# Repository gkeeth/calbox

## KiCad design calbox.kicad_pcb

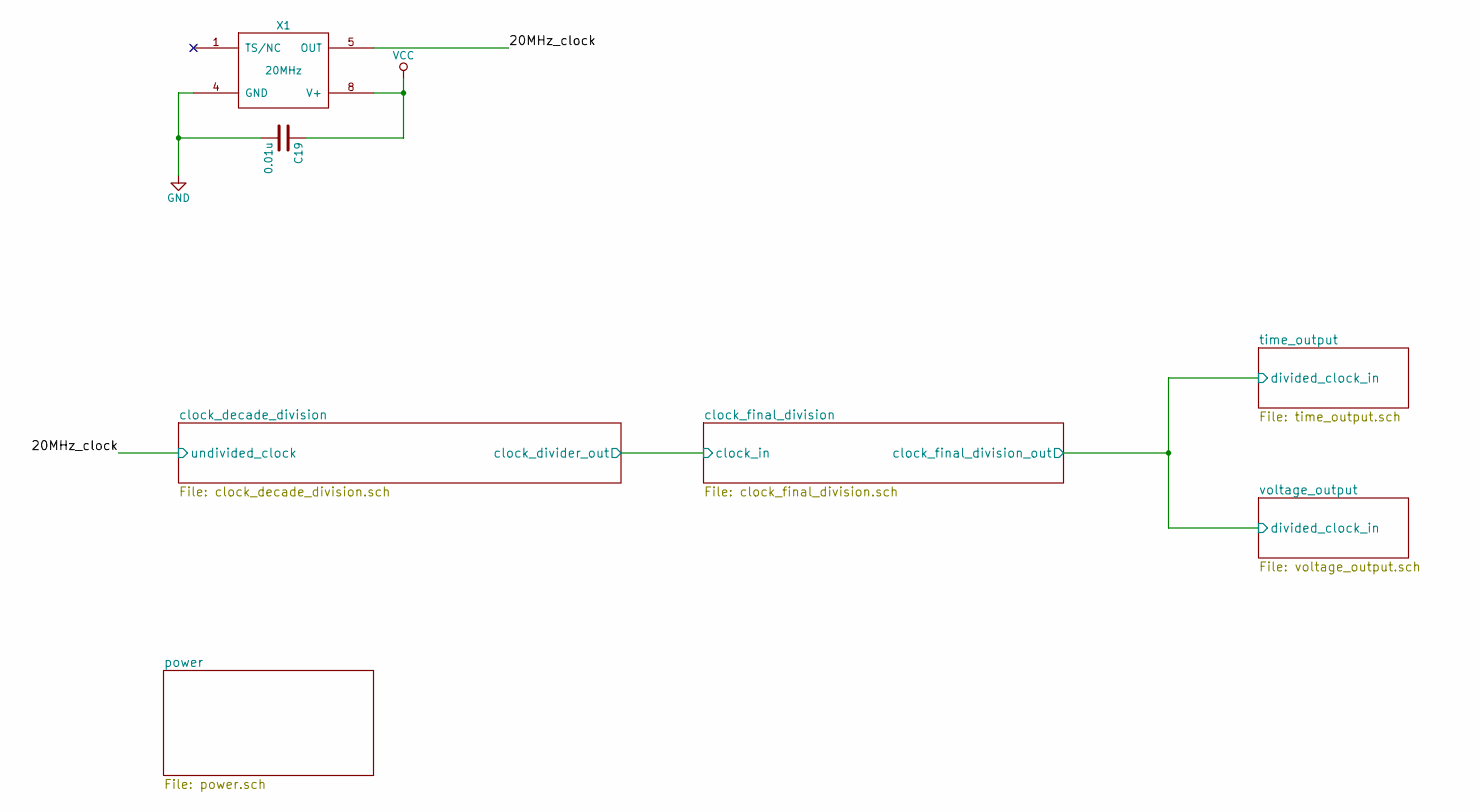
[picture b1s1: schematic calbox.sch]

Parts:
C19: 0.01u; C_0805_HandSoldering
X1: 20MHz; OSC_DIP8; Manufacturer PN ACHL-20.000MHZ-EK

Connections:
/20MHz_clock: X1.5 (OUT); also elsewhere on the board
GND: C19.2, X1.4 (GND); also elsewhere on the board
VCC: C19.1, X1.8 (V+); also elsewhere on the board

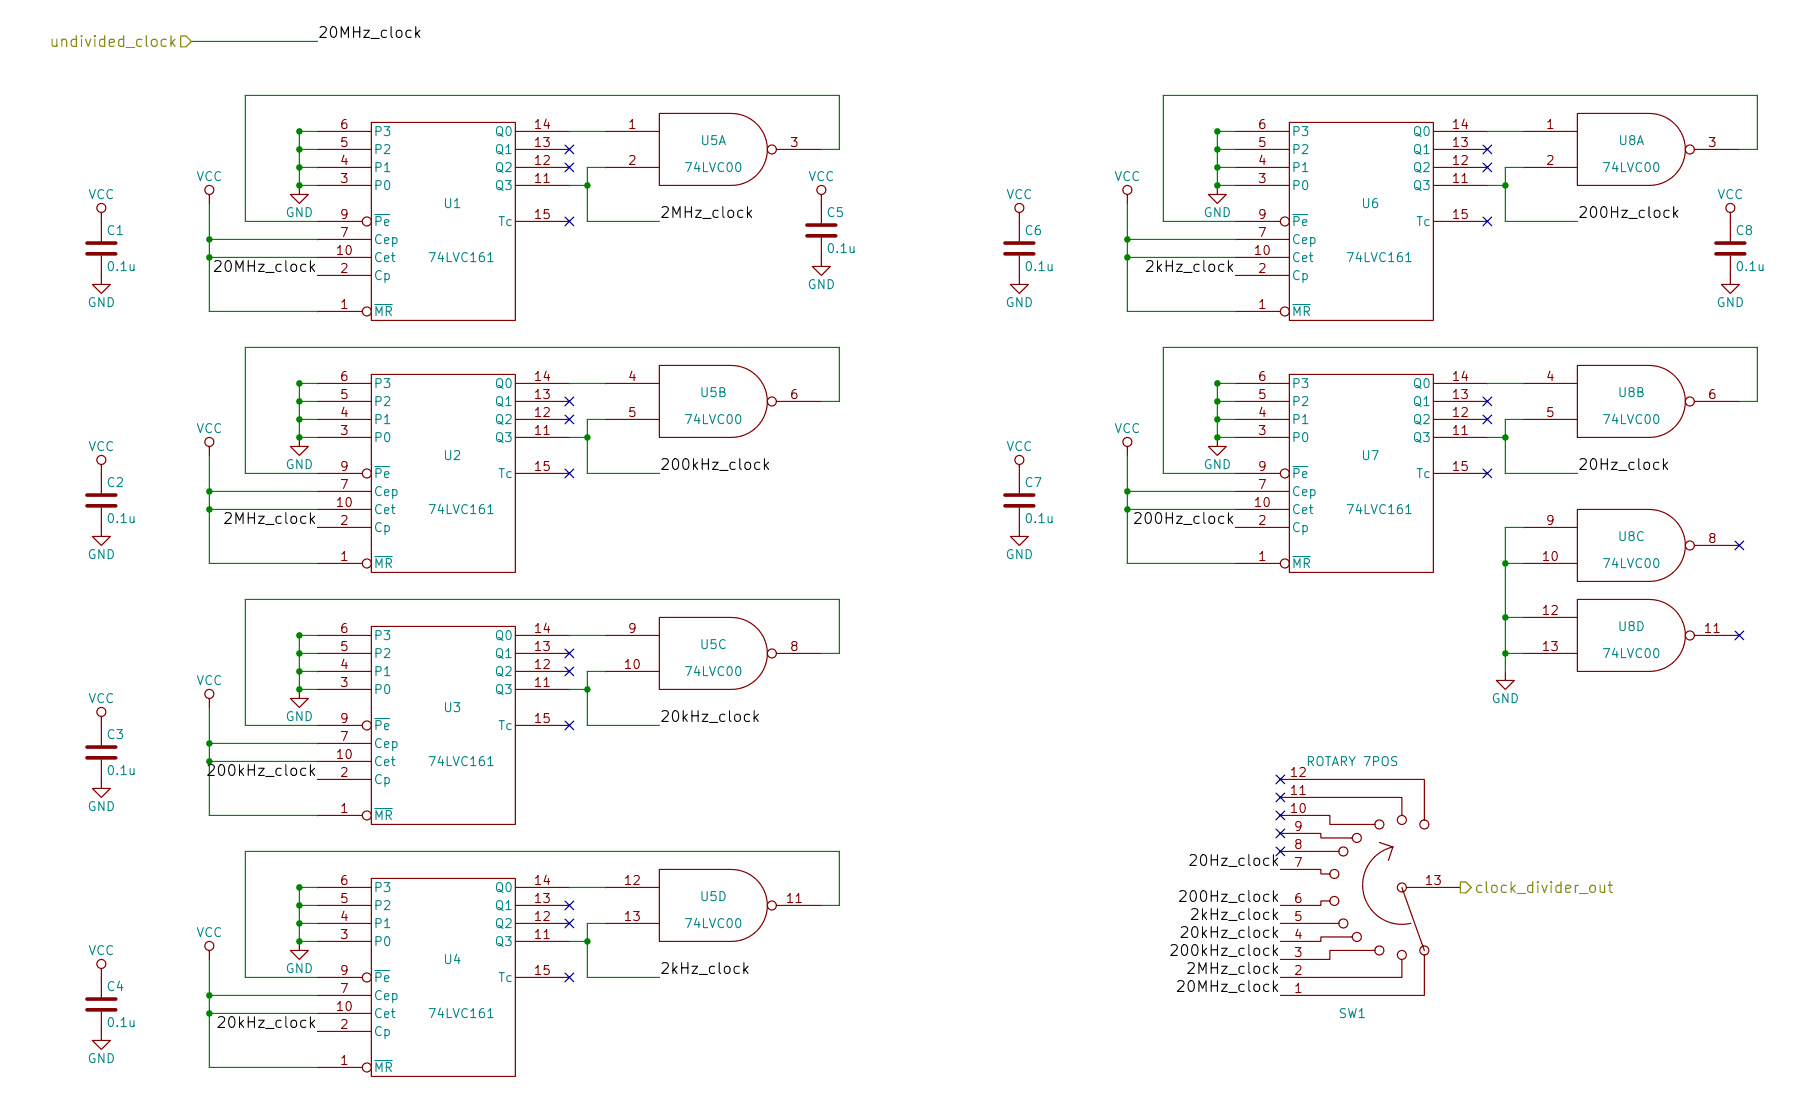
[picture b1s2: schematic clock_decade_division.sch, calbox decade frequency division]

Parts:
C1, C2, C3, C4, C5, C6, C7, C8: 0.1u; C_0805_HandSoldering
SW1: ROTARY 7POS; SW_ROTARY_SP12T_MRK112; Manufacturer PN MRK112-A
U1, U2, U3, U4, U6, U7: 74LVC161; SO-16-N; Manufacturer PN 4LVC161D118
U5, U8: 74LVC00; SOIC-14_N; Manufacturer PN SN74LVC00ADR

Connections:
/20MHz_clock: SW1.1, U1.2 (Cp); also elsewhere on the board
/clock_decade_division/2MHz_clock: SW1.2, U1.11 (Q3), U2.2 (Cp), U5.2
/clock_decade_division/2kHz_clock: SW1.5, U4.11 (Q3), U5.13, U6.2 (Cp)
/clock_decade_division/20Hz_clock: SW1.7, U7.11 (Q3), U8.5
/clock_decade_division/20kHz_clock: SW1.4, U3.11 (Q3), U4.2 (Cp), U5.10
/clock_decade_division/200Hz_clock: SW1.6, U6.11 (Q3), U7.2 (Cp), U8.2
/clock_decade_division/200kHz_clock: SW1.3, U2.11 (Q3), U3.2 (Cp), U5.5
/clock_decade_division/clock_divider_out: SW1.13; also elsewhere on the board
GND: C1.2, C2.2, C3.2, C4.2, C5.2, C6.2, C7.2, C8.2, U1.3 (P0), U1.4 (P1), U1.5 (P2), U1.6 (P3), U1.8 (GND), U2.3 (P0), U2.4 (P1), U2.5 (P2), U2.6 (P3), U2.8 (GND), U3.3 (P0), U3.4 (P1), U3.5 (P2), U3.6 (P3), U3.8 (GND), U4.3 (P0), U4.4 (P1), U4.5 (P2), U4.6 (P3), U4.8 (GND), U5.7 (GND), U6.3 (P0), U6.4 (P1), U6.5 (P2), U6.6 (P3), U6.8 (GND), U7.3 (P0), U7.4 (P1), U7.5 (P2), U7.6 (P3), U7.8 (GND), U8.7 (GND), U8.9, U8.10, U8.12, U8.13; also elsewhere on the board
unnamed: U1.9 (~Pe), U5.3
unnamed: U1.14 (Q0), U5.1
unnamed: U2.9 (~Pe), U5.6
unnamed: U2.14 (Q0), U5.4
unnamed: U3.9 (~Pe), U5.8
unnamed: U3.14 (Q0), U5.9
unnamed: U4.9 (~Pe), U5.11
unnamed: U4.14 (Q0), U5.12
unnamed: U6.9 (~Pe), U8.3
unnamed: U6.14 (Q0), U8.1
unnamed: U7.9 (~Pe), U8.6
unnamed: U7.14 (Q0), U8.4
VCC: C1.1, C2.1, C3.1, C4.1, C5.1, C6.1, C7.1, C8.1, U1.1 (~MR), U1.7 (Cep), U1.10 (Cet), U1.16 (VCC), U2.1 (~MR), U2.7 (Cep), U2.10 (Cet), U2.16 (VCC), U3.1 (~MR), U3.7 (Cep), U3.10 (Cet), U3.16 (VCC), U4.1 (~MR), U4.7 (Cep), U4.10 (Cet), U4.16 (VCC), U5.14 (VCC), U6.1 (~MR), U6.7 (Cep), U6.10 (Cet), U6.16 (VCC), U7.1 (~MR), U7.7 (Cep), U7.10 (Cet), U7.16 (VCC), U8.14 (VCC); also elsewhere on the board

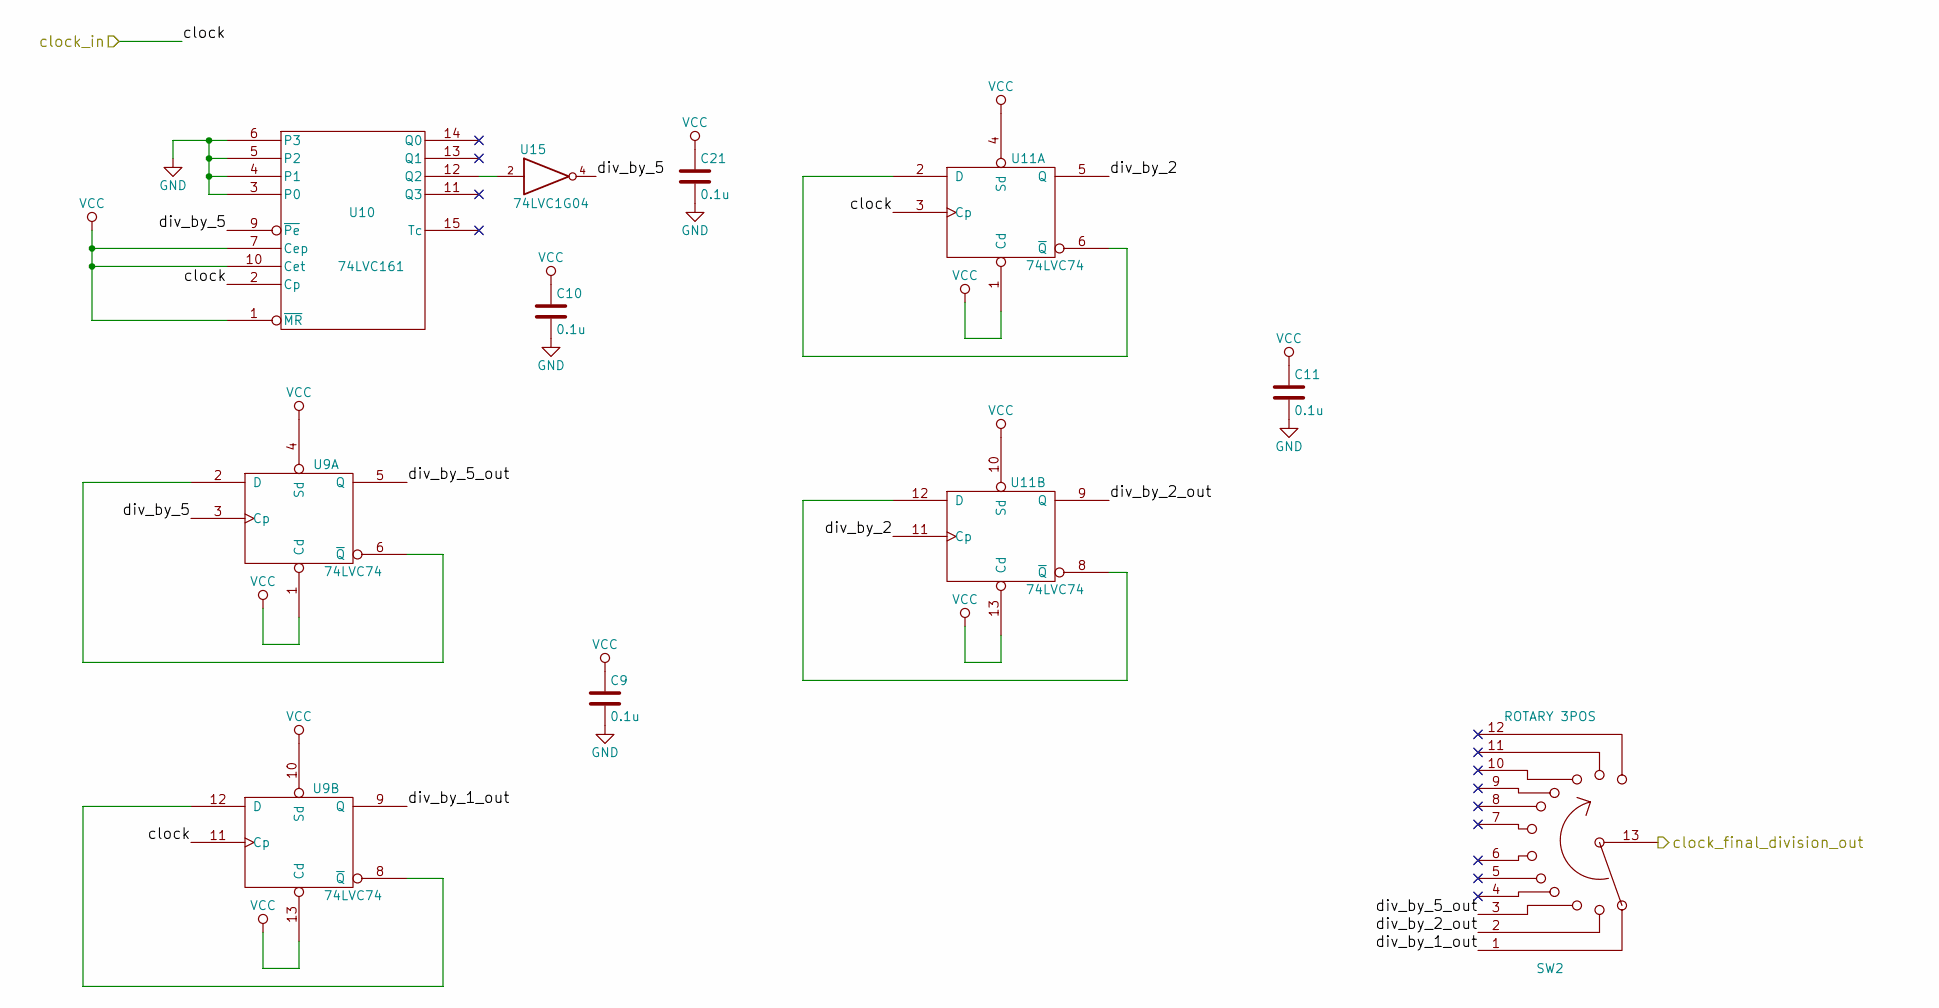
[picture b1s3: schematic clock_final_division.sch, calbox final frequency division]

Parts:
C9, C10, C11, C21: 0.1u; C_0805_HandSoldering
SW2: ROTARY 3POS; SW_ROTARY_SP12T_MRK112; Manufacturer PN MRK112-A
U9, U11: 74LVC74; SOIC-14_N; Manufacturer PN SN74LVC74ADR
U10: 74LVC161; SO-16-N; Manufacturer PN 4LVC161D118
U15: 74LVC1G04; SOT-23-5

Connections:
/clock_decade_division/clock_divider_out: U9.11 (Cp), U10.2 (Cp), U11.3 (Cp); also elsewhere on the board
/clock_final_division/clock_final_division_out: SW2.13; also elsewhere on the board
/clock_final_division/div_by_1_out: SW2.1, U9.9 (Q)
/clock_final_division/div_by_2: U11.5 (Q), U11.11 (Cp)
/clock_final_division/div_by_2_out: SW2.2, U11.9 (Q)
/clock_final_division/div_by_5: U9.3 (Cp), U10.9 (~Pe), U15.4
/clock_final_division/div_by_5_out: SW2.3, U9.5 (Q)
GND: C9.2, C10.2, C11.2, C21.2, U9.7 (GND), U10.3 (P0), U10.4 (P1), U10.5 (P2), U10.6 (P3), U10.8 (GND), U11.7 (GND), U15.3 (GND); also elsewhere on the board
unnamed: U9.2 (D), U9.6 (~Q)
unnamed: U9.8 (~Q), U9.12 (D)
unnamed: U10.12 (Q2), U15.2
unnamed: U11.2 (D), U11.6 (~Q)
unnamed: U11.8 (~Q), U11.12 (D)
VCC: C9.1, C10.1, C11.1, C21.1, U9.1 (Cd), U9.4 (Sd), U9.10 (Sd), U9.13 (Cd), U9.14 (VCC), U10.1 (~MR), U10.7 (Cep), U10.10 (Cet), U10.16 (VCC), U11.1 (Cd), U11.4 (Sd), U11.10 (Sd), U11.13 (Cd), U11.14 (VCC), U15.5 (VCC); also elsewhere on the board

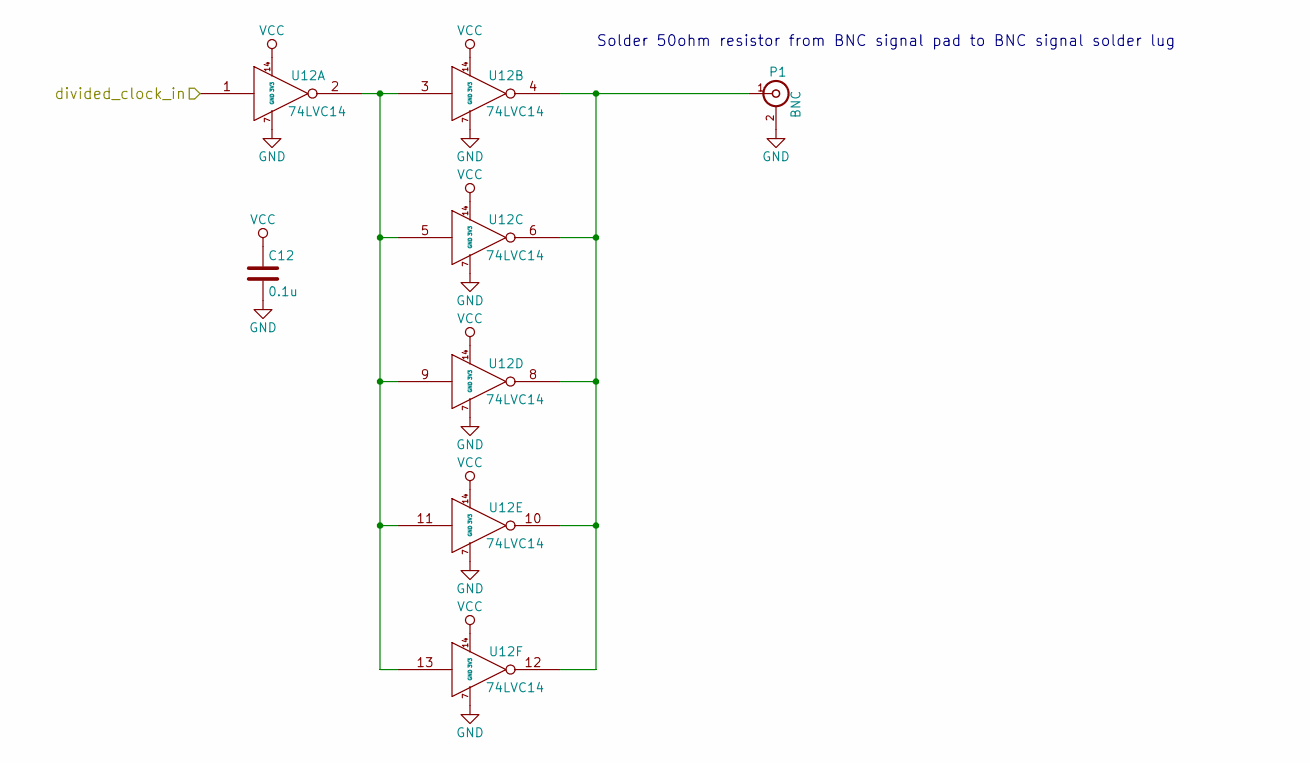
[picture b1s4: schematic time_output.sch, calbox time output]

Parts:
C12: 0.1u; C_0805_HandSoldering
P1: BNC; Pin_Header_Straight_1x02
U12: 74LVC14; SOIC-14_N; Manufacturer PN SN74LVC14ADR

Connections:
/clock_final_division/clock_final_division_out: U12.1; also elsewhere on the board
GND: C12.2, P1.2 (Ext), U12.7 (GND); also elsewhere on the board
unnamed: P1.1 (In), U12.4, U12.6, U12.8, U12.10, U12.12
unnamed: U12.2, U12.3, U12.5, U12.9, U12.11, U12.13
VCC: C12.1, U12.14 (3V3); also elsewhere on the board

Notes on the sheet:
Solder 50ohm resistor from BNC signal pad to BNC signal solder lug

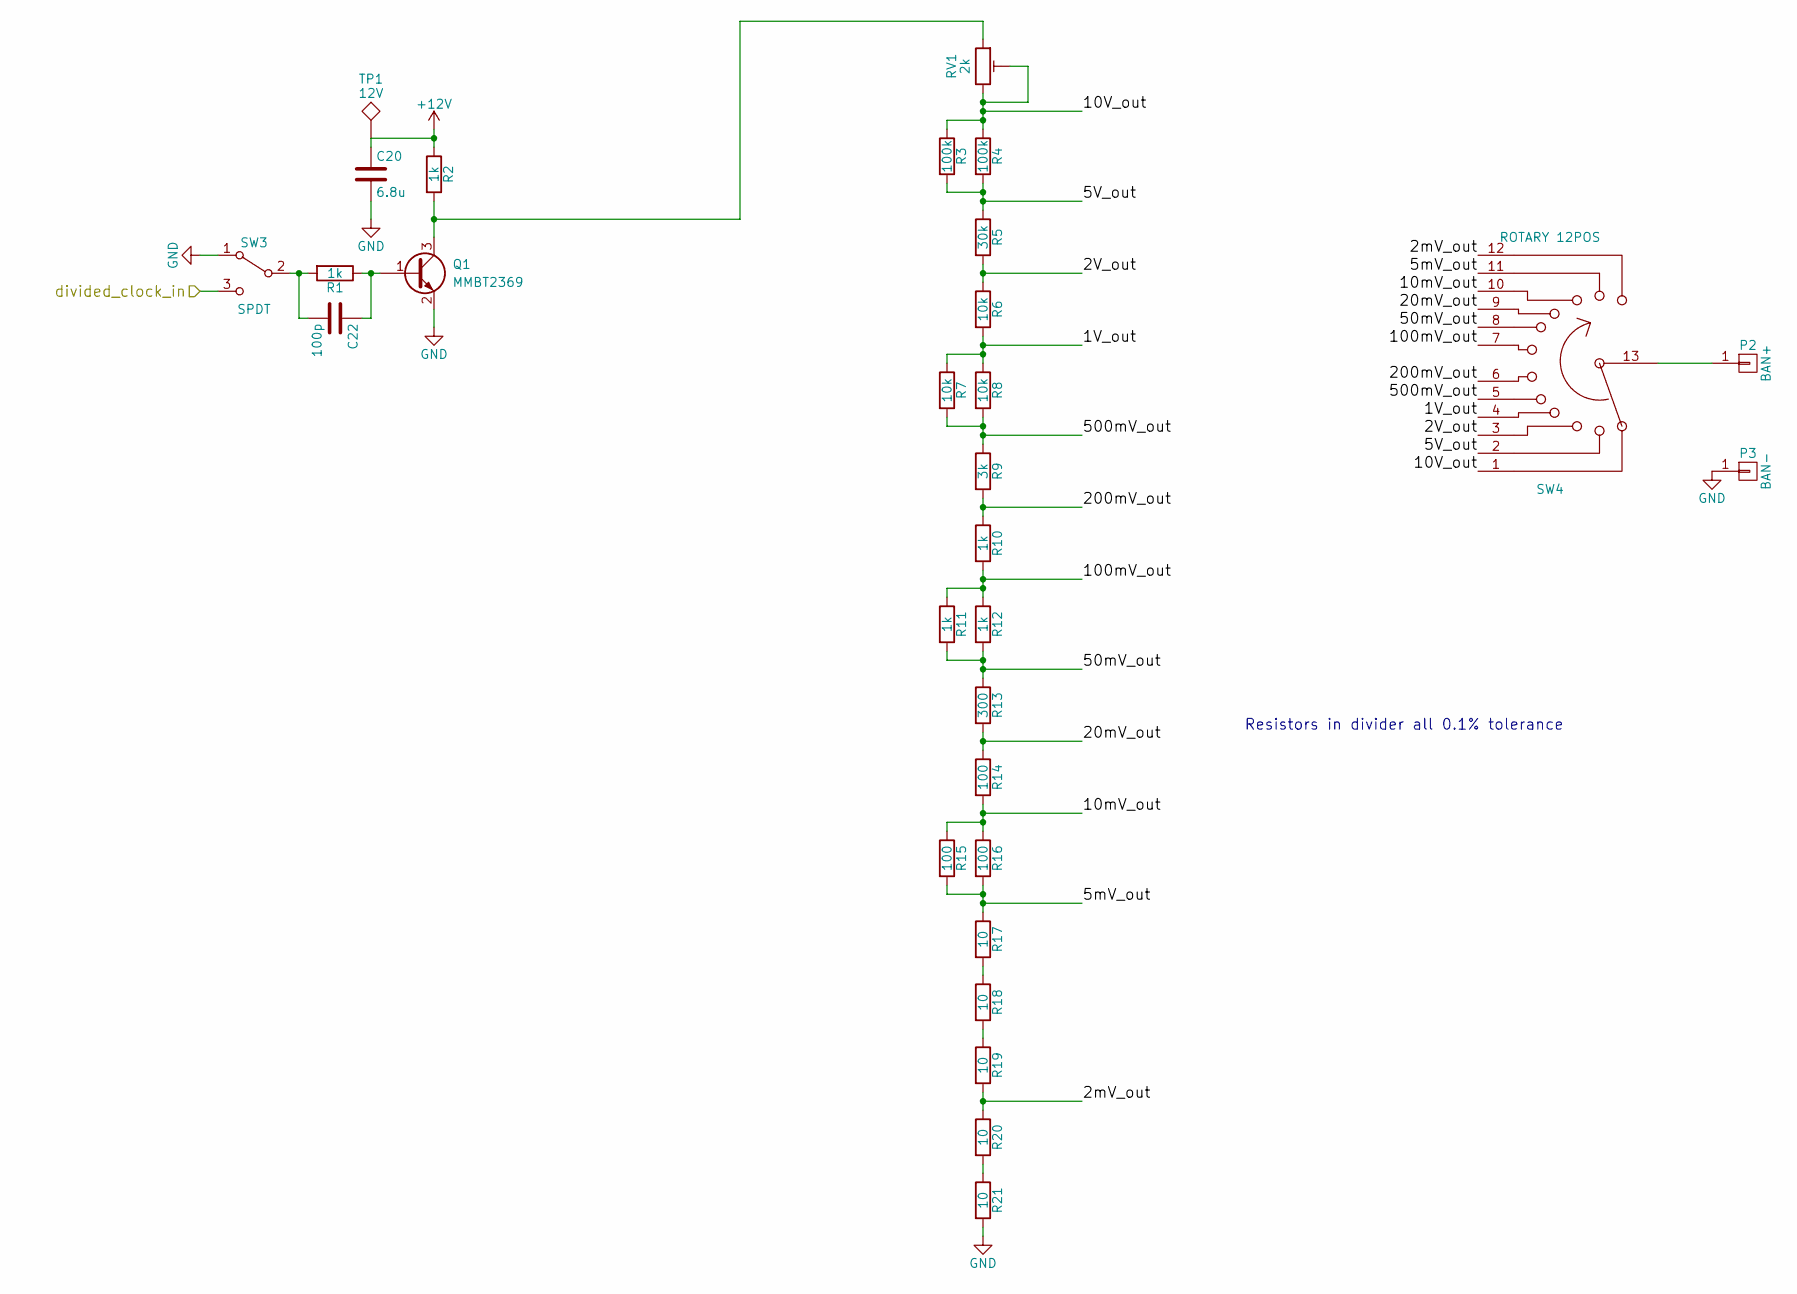
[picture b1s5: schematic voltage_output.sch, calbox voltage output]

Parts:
C20: 6.8u; C_0805_HandSoldering
C22: 100p; C_0805_HandSoldering
P2: BAN+; Pin_Header_Straight_1x01
P3: BAN-; Pin_Header_Straight_1x01
Q1: MMBT2369; SOT-23_Handsoldering; Manufacturer PN MMBT2369ALT1G
R1, R2, R10, R11, R12: 1k; R_0805_HandSoldering
R3, R4: 100k; R_0805_HandSoldering
R5: 30k; R_0805_HandSoldering
R6, R7, R8: 10k; R_0805_HandSoldering
R9: 3k; R_0805_HandSoldering
R13: 300; R_0805_HandSoldering
R14, R15, R16: 100; R_0805_HandSoldering
R17, R18, R19, R20, R21: 10; R_0805_HandSoldering
RV1: 2k; Potentiometer_Bourns_3362_ScrewUp; Manufacturer PN 3362P-1-202LF
SW3: SPDT; SW_SPDT_NKK_M201xxxx03; Manufacturer PN M2012SS1W03
SW4: ROTARY 12POS; SW_ROTARY_SP12T_MRK112; Manufacturer PN MRK112-A
TP1: 12V; Measurement_Point_Square-TH_Big

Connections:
+12V: C20.1, R2.1, TP1.1; also elsewhere on the board
/clock_final_division/clock_final_division_out: SW3.3 (C); also elsewhere on the board
/voltage_output/1V_out: R6.2, R7.1, R8.1, SW4.4
/voltage_output/2V_out: R5.2, R6.1, SW4.3
/voltage_output/2mV_out: R19.2, R20.1, SW4.12
/voltage_output/5V_out: R3.2, R4.2, R5.1, SW4.2
/voltage_output/5mV_out: R15.2, R16.2, R17.1, SW4.11
/voltage_output/10V_out: R3.1, R4.1, RV1.2, RV1.3, SW4.1
/voltage_output/10mV_out: R14.2, R15.1, R16.1, SW4.10
/voltage_output/20mV_out: R13.2, R14.1, SW4.9
/voltage_output/50mV_out: R11.2, R12.2, R13.1, SW4.8
/voltage_output/100mV_out: R10.2, R11.1, R12.1, SW4.7
/voltage_output/200mV_out: R9.2, R10.1, SW4.6
/voltage_output/500mV_out: R7.2, R8.2, R9.1, SW4.5
GND: C20.2, P3.1, Q1.2 (E), R21.2, SW3.1 (A); also elsewhere on the board
unnamed: C22.1, Q1.1 (B), R1.1
unnamed: C22.2, R1.2, SW3.2 (B)
unnamed: P2.1, SW4.13
unnamed: Q1.3 (C), R2.2, RV1.1
unnamed: R17.2, R18.1
unnamed: R18.2, R19.1
unnamed: R20.2, R21.1

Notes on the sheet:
Resistors in divider all 0.1% tolerance

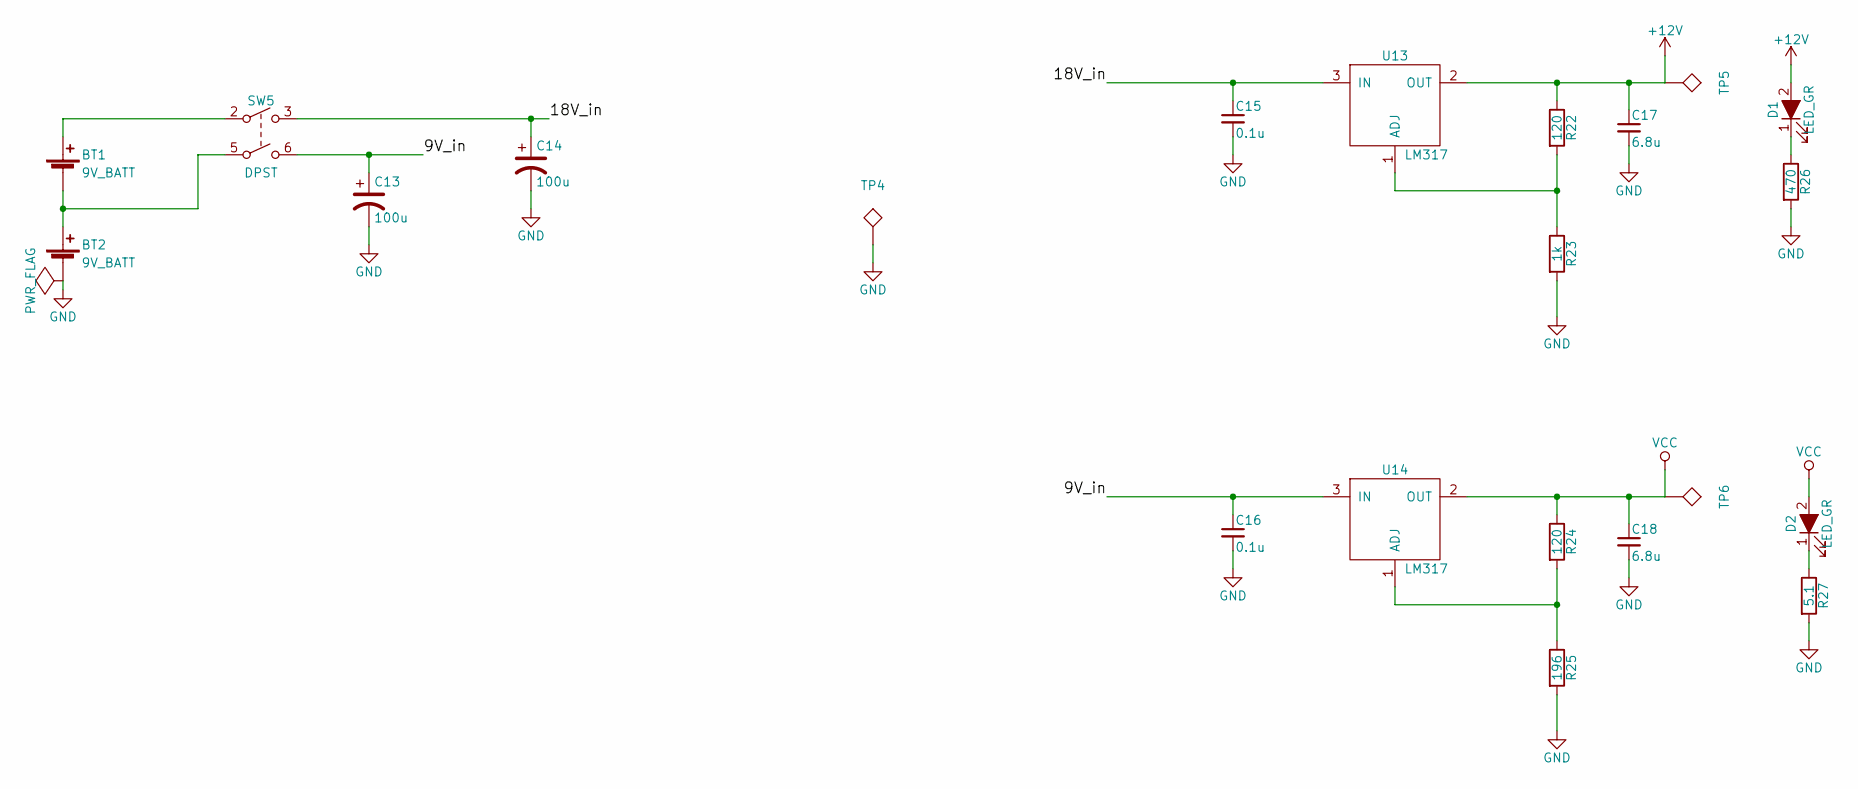
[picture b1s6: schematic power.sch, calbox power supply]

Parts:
BT1, BT2: 9V_BATT; battery_snap
C13, C14: 100u; C_Radial_D6.3_L11.2_P2.5; Manufacturer PN URS1E101MDD
C15, C16: 0.1u; C_0805_HandSoldering
C17, C18: 6.8u; C_0805_HandSoldering
D1, D2: LED_GR; LED-5MM; Manufacturer PN C503B-GCN-CY0C0792
R22, R24: 120; R_0805_HandSoldering
R23: 1k; R_0805_HandSoldering
R25: 196; R_0805_HandSoldering
R26: 470; R_0805_HandSoldering
R27: 5.1; R_0805_HandSoldering
SW5: DPST; SW_NKK_M20xxxxx03_DPST; Manufacturer PN M2021SS1W03
TP4: GND; Measurement_Point_Square-TH_Big
TP5: 12V; Measurement_Point_Square-TH_Big
TP6: 3.3V; Measurement_Point_Square-TH_Big
U13, U14: LM317; SOT-223; Manufacturer PN LM317DCYR

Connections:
+12V: C17.1, D1.2 (A), R22.1, TP5.1, U13.2 (OUT), U13.4 (OUT); also elsewhere on the board
/power/9V_in: C13.1, C16.1, SW5.6, U14.3 (IN)
/power/18V_in: C14.1, C15.1, SW5.3, U13.3 (IN)
GND: BT2.2 (-), C13.2, C14.2, C15.2, C16.2, C17.2, C18.2, R23.2, R25.2, R26.2, R27.2, TP4.1; also elsewhere on the board
unnamed: BT1.1 (+), SW5.2
unnamed: BT1.2 (-), BT2.1 (+), SW5.5
unnamed: D1.1 (K), R26.1
unnamed: D2.1 (K), R27.1
unnamed: R22.2, R23.1, U13.1 (ADJ)
unnamed: R24.2, R25.1, U14.1 (ADJ)
VCC: C18.1, D2.2 (A), R24.1, TP6.1, U14.2 (OUT), U14.4 (OUT); also elsewhere on the board

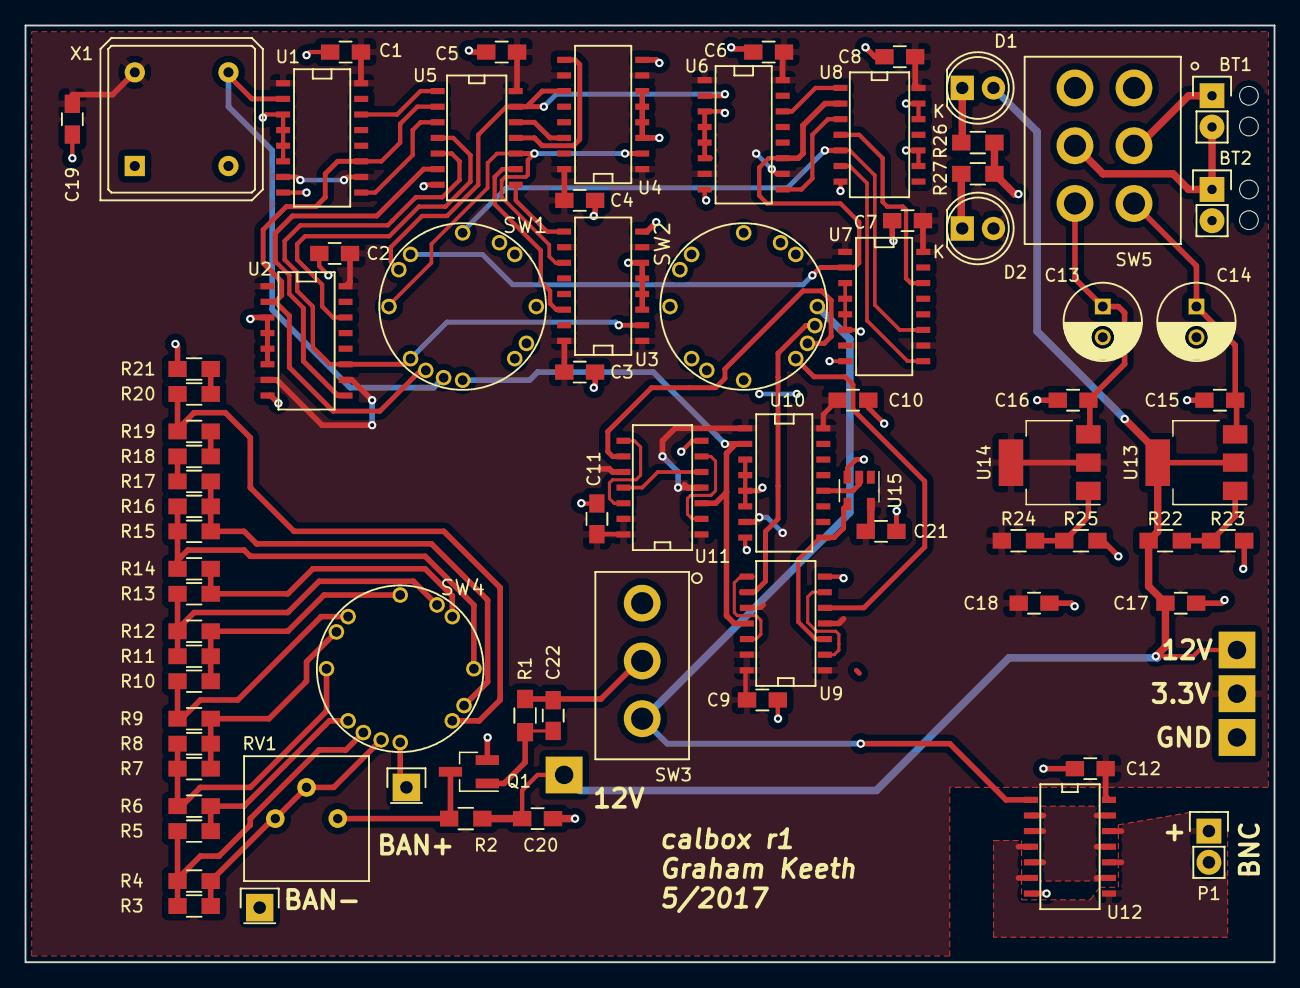
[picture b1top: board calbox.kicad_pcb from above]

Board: 2 copper layers, 101.6 x 76.2 mm, 83 parts (0 on the bottom side), 63 nets.

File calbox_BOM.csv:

Source,/Users/graham/projects/calbox/calbox.sch
Kicad Rev,Eeschema 4.0.5
Generated Date,Sunday, March 19, 2017 'PMt' 10:40:55 PM

Title,calbox
Company,Not Set
Revision,Not Set
Date Issue,Not Set

Reference,Value,Manufacturer,Manufacturer PN,Distributor,Distributor PN,URL,Unit Price,Library,Library Ref
C19,0.01u,device,C
X1,20MHz,ABRACON,ACHL-20.000MHZ-EK,Mouser,815-ACHL-20-EK,http://www.mouser.com/Search/ProductDetail.aspx?R=ACHL-20.00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,1.76,calbox,ACHL_XO
C1,0.1u,device,C
C2,0.1u,device,C
C4,0.1u,device,C
C3,0.1u,device,C
C5,0.1u,device,C
C6,0.1u,device,C
C7,0.1u,device,C
C8,0.1u,device,C
U5,74LVC00,TI,SN74LVC00ADR,Mouser,595-SN74LVC00ADR,http://www.mouser.com/Search/ProductDetail.aspx?R=SN74LVC00A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,0.40,calbox,74LVC00
U1,74LVC161,Nexperia,4LVC161D118,Mouser,771-LVC161D118,http://www.mouser.com/Search/ProductDetail.aspx?R=74LVC161D%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,0.61,calbox,74LVC161
SW1,FREQ SWITCH 1,NKK,MRK112-A,Mouser,633-MRK112A,http://www.mouser.com/Search/ProductDetail.aspx?R=MRK112-Avi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,11.80,switches,SW_Rotary12
U2,74LVC161,Nexperia,4LVC161D118,Mouser,771-LVC161D118,http://www.mouser.com/Search/ProductDetail.aspx?R=74LVC161D%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,0.61,calbox,74LVC161
U3,74LVC161,Nexperia,4LVC161D118,Mouser,771-LVC161D118,http://www.mouser.com/Search/ProductDetail.aspx?R=74LVC161D%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,0.61,calbox,74LVC161
U4,74LVC161,Nexperia,4LVC161D118,Mouser,771-LVC161D118,http://www.mouser.com/Search/ProductDetail.aspx?R=74LVC161D%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,0.61,calbox,74LVC161
U6,74LVC161,Nexperia,4LVC161D118,Mouser,771-LVC161D118,http://www.mouser.com/Search/ProductDetail.aspx?R=74LVC161D%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,0.61,calbox,74LVC161
U7,74LVC161,Nexperia,4LVC161D118,Mouser,771-LVC161D118,http://www.mouser.com/Search/ProductDetail.aspx?R=74LVC161D%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,0.61,calbox,74LVC161
U8,74LVC00,TI,SN74LVC00ADR,Mouser,595-SN74LVC00ADR,http://www.mouser.com/Search/ProductDetail.aspx?R=SN74LVC00A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,0.40,calbox,74LVC00
C10,0.1u,device,C
C9,0.1u,device,C
C11,0.1u,device,C
U9,74LVC74,TI,SN74LVC74ADR,Mouser,595-SN74LVC74ADR,http://www.mouser.com/Search/ProductDetail.aspx?R=SN74LVC74A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,0.40,calbox,74LVC74
SW2,FREQ SWITCH 2,NKK,MRK112-A,Mouser,633-MRK112A,http://www.mouser.com/Search/ProductDetail.aspx?R=MRK112-Avi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,11.80,switches,SW_Rotary12
U10,74LVC161,Nexperia,4LVC161D118,Mouser,771-LVC161D118,http://www.mouser.com/Search/ProductDetail.aspx?R=74LVC161D%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,0.61,calbox,74LVC161
U11,74LVC74,TI,SN74LVC74ADR,Mouser,595-SN74LVC74ADR,http://www.mouser.com/Search/ProductDetail.aspx?R=SN74LVC74A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,0.40,calbox,74LVC74
P1,BNC,conn,BNC
U12,74LVC14,TI,SN74LVC14ADR,Mouser,595-SN74LVC14ADR,http://www.mouser.com/Search/ProductDetail.aspx?R=SN74LVC14A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,0.40,calbox,74LVC14
C12,0.1u,device,C
P2,BAN+,conn,CONN_01X01
P3,BAN-,conn,CONN_01X01
R10,1k,device,R
R12,1k,device,R
R13,300,device,R
R14,100,device,R
R16,100,device,R
R17,10,device,R
R21,10,device,R
SW3,SPDT,NKK,M2012SS1W03,Mouser,633-M201203,http://www.mouser.com/Search/ProductDetail.aspx?R=M2012SS1W0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,2.86,switches,SW_SPDT
RV1,2k,Bourns,3362P-1-202LF,Mouser,652-3362P-1-202LF,http://www.mouser.com/Search/ProductDetail.aspx?R=3362P-1-20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,1.02,device,POT_TRIM
SW4,VOLTAGE SWITCH,NKK,MRK112-A,Mouser,633-MRK112A,http://www.mouser.com/Search/ProductDetail.aspx?R=MRK112-Avi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,11.80,switches,SW_Rotary12
R9,3k,device,R
R8,10k,device,R
R6,10k,device,R
R4,100k,device,R
R5,30k,device,R
Q1,MMBT2369,ON Semiconductor,MMBT2369ALT1G,Mouser,863-MMBT2369ALT1G,http://www.mouser.com/Search/ProductDetail.aspx?R=MMBT2369AL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,0.19,device,Q_NPN_BEC
R2,1k,device,R
R1,470,device,R
C20,6.8u,device,C
TP1,TEST,device,TEST
R3,100k,device,R
R7,10k,device,R
R11,1k,device,R
R15,100,device,R
R18,10,device,R
R19,10,device,R
R20,10,device,R
BT1,9V_BATT,device,Battery_Cell
BT2,9V_BATT,device,Battery_Cell
R24,120,device,R
R25,200,device,R
C16,0.1u,device,C_Small
C18,6.8u,device,C_Small
R22,120,device,R
R23,1k,device,R
C15,0.1u,device,C_Small
C17,6.8u,device,C_Small
C13,100u,Nichicon,URS1E101MDD,Mouser,647-URS1E101MDD,http://www.mouser.com/Search/ProductDetail.aspx?R=URS1E101MD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,0.34,device,CP1
D1,LED_GR,Cree,C503B-GCN-CY0C0792,Mouser,941-C503BGCNCY0C0792,http://www.mouser.com/Search/ProductDetail.aspx?R=C503B-GCN-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,0.24,device,LED_ALT
R27,5,device,R
R26,470,device,R
SW5,DPST,NKK,M2021SS1W03,Mouser,633-M2021SS1W03,http://www.mouser.com/Search/ProductDetail.aspx?R=M2021SS1W0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,4.32,calbox,SW_DPST_NKK_M2021
U13,LM317,TI,LM317DCYR,Mouser,595-LM317DCYR,http://www.mouser.com/Search/ProductDetail.aspx?R=LM317DCYRv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,0.74,calbox,LM317_SOT223_4pin
TP5,12V,device,TEST
TP6,3.3V,device,TEST
TP4,GND,device,TEST
U14,LM317,TI,LM317DCYR,Mouser,595-LM317DCYR,http://www.mouser.com/Search/ProductDetail.aspx?R=LM317DCYRv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,0.74,calbox,LM317_SOT223_4pin
D2,LED_GR,Cree,C503B-GCN-CY0C0792,Mouser,941-C503BGCNCY0C0792,http://www.mouser.com/Search/ProductDetail.aspx?R=C503B-GCN-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,0.24,device,LED_ALT
C14,100u,Nichicon,URS1E101MDD,Mouser,647-URS1E101MDD,http://www.mouser.com/Search/ProductDetail.aspx?R=URS1E101MD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,0.34,device,CP1

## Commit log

2017-03-16 Initial content commit. Schematic nearly finished; needs resistor divider values, a bypass cap on +12V, and test points. Layout r1 finished.
2017-03-16 Ignored backup (*.bak) files
2017-03-16 ignored .DS_Store file
2017-03-16 Create LICENSE
2017-03-16 Ignore *.kicad_pcb-bak files
2017-03-16 Added bypass capacitor to +12V line
2017-03-16 Added sim/ folder for simulations
2017-03-16 Added testpoints for VCC, 12V, and GND
2017-03-16 Added first pass of script to calculate optimum resistor values for voltage output divider
2017-03-18 Updated calculate_resistors.py to choose the best combination and do some basic error analysis
2017-03-18 Updated voltage output divider to use practical resistor values
2017-03-19 R2 PCB rotary switches closer to middle of board
2017-03-26 update switch models in library, rotate final clock division switch
2017-03-26 add dimensions to pcb
2017-03-26 updated layout, specifically banana plug attachment points
2017-03-26 reorganize repo
2017-03-26 version sent to EasyEDA 3/26/17
2017-04-17 Several schematic & layout changes after building first boards
    - increase current limiting resistors on LEDs to make them less blinding
    - add speedup cap, increase base resistor on voltage output switching
    transistor for better high frequency performance (should work up to 10MHz)
    - change switched/constant voltage output toggle switch to actually work
    (now toggles between switched voltage output and constant voltage
    output, rather than switched and 0V output)
2017-04-17 update layout for div-by-5 inverter
2017-04-17 update voltage output schematic
2017-05-23 Add battery snap footprint with stress relief NPTHs
2017-05-23 Update schematic for rev1
    - add battery snap footprint
    - add speedup cap for voltage output transistor
    - correct voltage output toggle switch operation (vcc -> gnd for
    constant voltage output)
    - add single gate inverter for correct divide-by-10 operation
2017-05-23 Layout changes for r1
2017-05-23 Update battery snap footprint NPTHs to be bigger and actually non-plated
2017-05-23 Updated layout, gerbers, and layout pdf for enlarged battery non-plated through holes
2017-05-23 minor layout update
2017-05-23 Update gerbers to not have sheet headers
2017-05-23 remove unnecessary fab drawing from gerbers
2017-05-26 Update BOM and add formatted BOM
2017-07-03 update dimensions for LED holes in case
